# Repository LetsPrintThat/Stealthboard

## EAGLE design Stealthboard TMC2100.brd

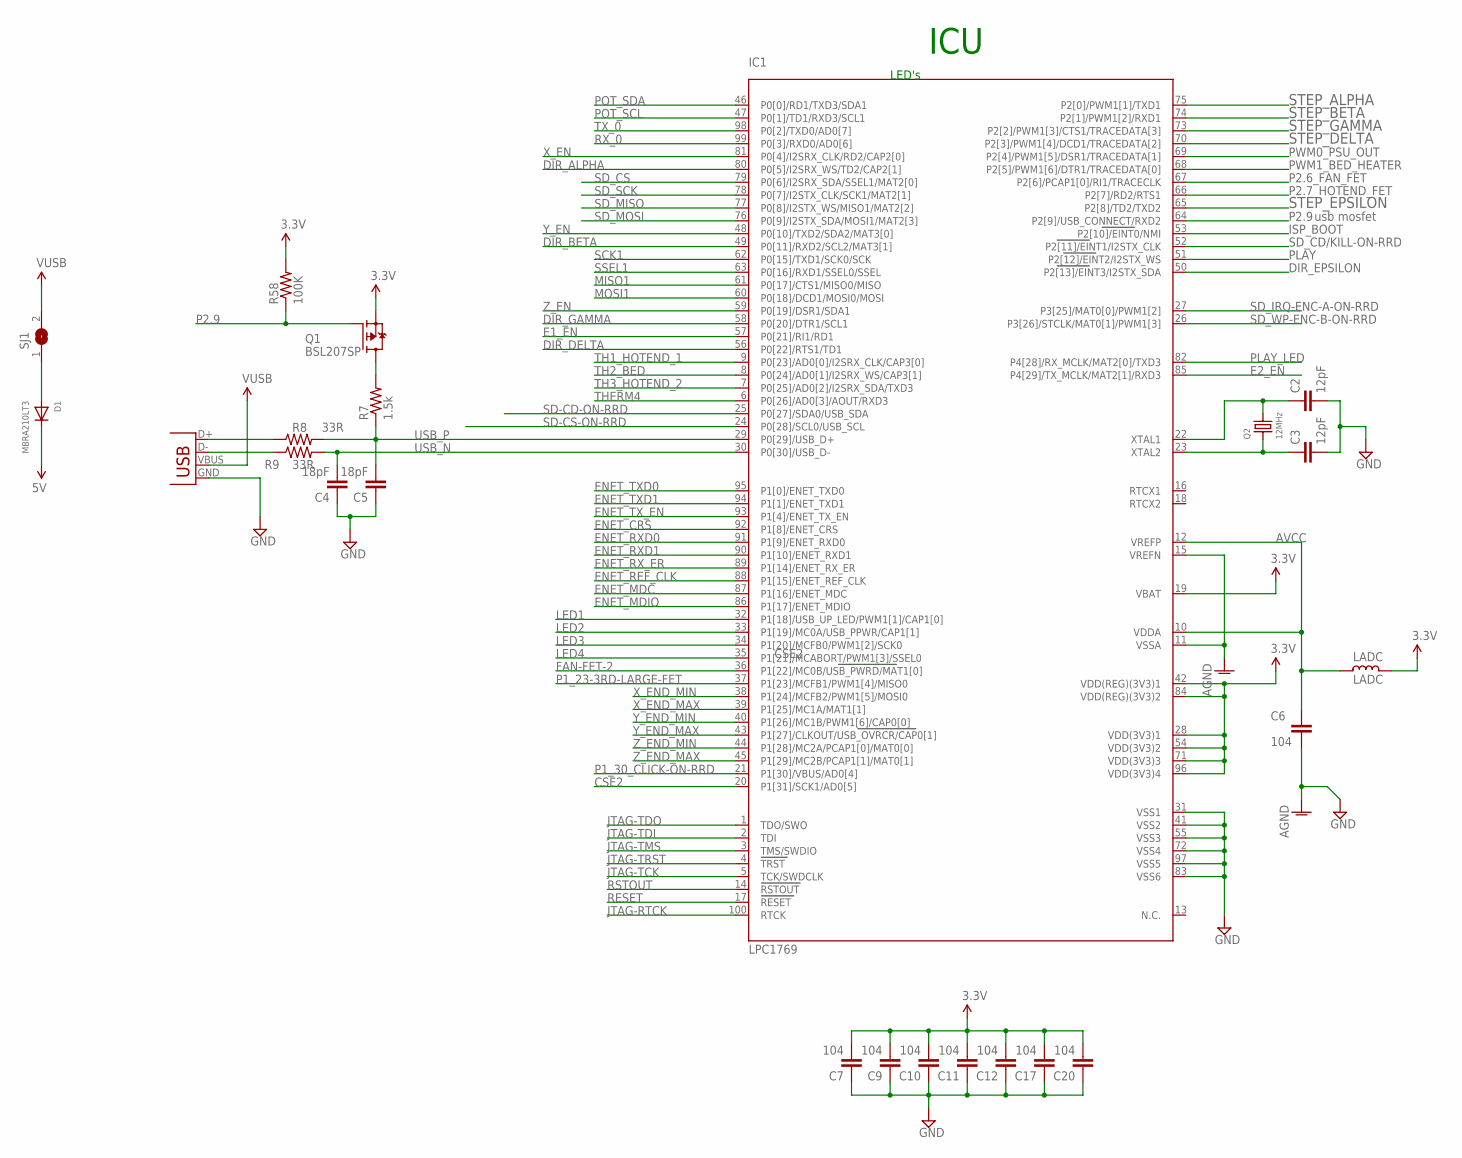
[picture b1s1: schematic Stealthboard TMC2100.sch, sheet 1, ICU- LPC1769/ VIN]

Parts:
C2, C3: 12pF; C0402
C4, C5: 18pF; C0402
C6, C7, C9, C10, C11, C12, C17, C20: 104; C0402
D1: MBRA210LT3; SMADIODE
IC1: LPC1769; LQFP100
LADC: LADC; L0402_LPT
Q1: BSL207SP; SC74_INFINEON
Q2: 12MHz; CRYSTAL_3.2X2.5
R7: 1.5k; R0402
R8, R9: 33R; R0402
R58: 100K; R0402
SJ1: SJ
X14: USBPTH; USB-B-PTH

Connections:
3.3V: C7.2, C9.2, C10.2, C11.2, C12.2, C17.2, C20.2, IC1.19 (VBAT), IC1.28 (VDD(3V3)1), IC1.42 (VDD(REG)(3V3)1), IC1.54 (VDD(3V3)2), IC1.71 (VDD(3V3)3), IC1.84 (VDD(REG)(3V3)2), IC1.96 (VDD(3V3)4), LADC.1, Q1.4 (S), R58.2; also elsewhere on the board
5V: D1.C; also elsewhere on the board
AGND: C6.2, IC1.11 (VSSA), IC1.15 (VREFN); also elsewhere on the board
AVCC: C6.1, IC1.10 (VDDA), IC1.12 (VREFP), LADC.2; also elsewhere on the board
CSE2: IC1.20 (P1[31]/SCK1/AD0[5])
DIR_ALPHA: IC1.80 (P0[5]/I2SRX_WS/TD2/CAP2[1]); also elsewhere on the board
DIR_BETA: IC1.49 (P0[11]/RXD2/SCL2/MAT3[1]); also elsewhere on the board
DIR_DELTA: IC1.56 (P0[22]/RTS1/TD1); also elsewhere on the board
DIR_EPSILON: IC1.50 (P2[13]/EINT3/I2STX_SDA); also elsewhere on the board
DIR_GAMMA: IC1.58 (P0[20]/DTR1/SCL1); also elsewhere on the board
E1_EN: IC1.57 (P0[21]/RI1/RD1); also elsewhere on the board
E2_EN: IC1.85 (P4[29]/TX_MCLK/MAT2[1]/RXD3); also elsewhere on the board
ENET_CRS: IC1.92 (P1[8]/ENET_CRS); also elsewhere on the board
ENET_MDC: IC1.87 (P1[16]/ENET_MDC); also elsewhere on the board
ENET_MDIO: IC1.86 (P1[17]/ENET_MDIO); also elsewhere on the board
ENET_REF_CLK: IC1.88 (P1[15]/ENET_REF_CLK); also elsewhere on the board
ENET_RXD0: IC1.91 (P1[9]/ENET_RXD0); also elsewhere on the board
ENET_RXD1: IC1.90 (P1[10]/ENET_RXD1); also elsewhere on the board
ENET_RX_ER: IC1.89 (P1[14]/ENET_RX_ER)
ENET_TXD0: IC1.95 (P1[0]/ENET_TXD0); also elsewhere on the board
ENET_TXD1: IC1.94 (P1[1]/ENET_TXD1); also elsewhere on the board
ENET_TX_EN: IC1.93 (P1[4]/ENET_TX_EN); also elsewhere on the board
FAN-FET-2: IC1.36 (P1[22]/MC0B/USB_PWRD/MAT1[0]); also elsewhere on the board
GND: C2.2, C3.2, C4.1, C5.1, C7.1, C9.1, C10.1, C11.1, C12.1, C17.1, C20.1, IC1.31 (VSS1), IC1.41 (VSS2), IC1.55 (VSS3), IC1.72 (VSS4), IC1.83 (VSS6), IC1.97 (VSS5), X14.GND; also elsewhere on the board
ISP_BOOT: IC1.53 (P2[10]/EINT0/NMI); also elsewhere on the board
JTAG-RTCK: IC1.100 (RTCK)
JTAG-TCK: IC1.5 (TCK/SWDCLK)
JTAG-TDI: IC1.2 (TDI)
JTAG-TDO: IC1.1 (TDO/SWO)
JTAG-TMS: IC1.3 (TMS/SWDIO)
JTAG-TRST: IC1.4 (TRST)
LED1: IC1.32 (P1[18]/USB_UP_LED/PWM1[1]/CAP1[0]); also elsewhere on the board
LED2: IC1.33 (P1[19]/MC0A/USB_PPWR/CAP1[1]); also elsewhere on the board
LED3: IC1.34 (P1[20]/MCFB0/PWM1[2]/SCK0); also elsewhere on the board
LED4: IC1.35 (P1[21]/MCABORT/PWM1[3]/SSEL0); also elsewhere on the board
MISO1: IC1.61 (P0[17]/CTS1/MISO0/MISO); also elsewhere on the board
MOSI1: IC1.60 (P0[18]/DCD1/MOSI0/MOSI); also elsewhere on the board
unnamed: C2.1, IC1.22 (XTAL1), Q2.2
unnamed: C3.1, IC1.23 (XTAL2), Q2.1
unnamed: D1.A, SJ1.1
unnamed: Q1.1 (D), Q1.2 (D), Q1.5 (D), Q1.6 (D), R7.2
unnamed: R8.1, X14.D+
unnamed: R9.1, X14.D-
P1_23-3RD-LARGE-FET: IC1.37 (P1[23]/MCFB1/PWM1[4]/MISO0); also elsewhere on the board
P1_30_CLICK-ON-RRD: IC1.21 (P1[30]/VBUS/AD0[4]); also elsewhere on the board
P2.6_FAN_FET: IC1.67 (P2[6]/PCAP1[0]/RI1/TRACECLK); also elsewhere on the board
P2.7_HOTEND_FET: IC1.66 (P2[7]/RD2/RTS1); also elsewhere on the board
P2.9: IC1.64 (P2[9]/USB_CONNECT/RXD2), Q1.3 (G), R58.1
PLAY: IC1.51 (P2[12]/EINT2/I2STX_WS); also elsewhere on the board
PLAY_LED: IC1.82 (P4[28]/RX_MCLK/MAT2[0]/TXD3); also elsewhere on the board
POT_SCL: IC1.47 (P0[1]/TD1/RXD3/SCL1); also elsewhere on the board
POT_SDA: IC1.46 (P0[0]/RD1/TXD3/SDA1); also elsewhere on the board
PWM0_PSU_OUT: IC1.69 (P2[4]/PWM1[5]/DSR1/TRACEDATA[1]); also elsewhere on the board
PWM1_BED_HEATER: IC1.68 (P2[5]/PWM1[6]/DTR1/TRACEDATA[0]); also elsewhere on the board
RESET: IC1.17 (RESET); also elsewhere on the board
RSTOUT: IC1.14 (RSTOUT)
RX_0: IC1.99 (P0[3]/RXD0/AD0[6]); also elsewhere on the board
SCK1: IC1.62 (P0[15]/TXD1/SCK0/SCK); also elsewhere on the board
SD-CD-ON-RRD: IC1.25 (P0[27]/SDA0/USB_SDA); also elsewhere on the board
SD-CS-ON-RRD: IC1.24 (P0[28]/SCL0/USB_SCL); also elsewhere on the board
SD_CD/KILL-ON-RRD: IC1.52 (P2[11]/EINT1/I2STX_CLK); also elsewhere on the board
SD_CS: IC1.79 (P0[6]/I2SRX_SDA/SSEL1/MAT2[0]); also elsewhere on the board
SD_IRQ-ENC-A-ON-RRD: IC1.27 (P3[25]/MAT0[0]/PWM1[2]); also elsewhere on the board
SD_MISO: IC1.77 (P0[8]/I2STX_WS/MISO1/MAT2[2]); also elsewhere on the board
SD_MOSI: IC1.76 (P0[9]/I2STX_SDA/MOSI1/MAT2[3]); also elsewhere on the board
SD_SCK: IC1.78 (P0[7]/I2STX_CLK/SCK1/MAT2[1]); also elsewhere on the board
SD_WP-ENC-B-ON-RRD: IC1.26 (P3[26]/STCLK/MAT0[1]/PWM1[3]); also elsewhere on the board
SSEL1: IC1.63 (P0[16]/RXD1/SSEL0/SSEL); also elsewhere on the board
STEP_ALPHA: IC1.75 (P2[0]/PWM1[1]/TXD1); also elsewhere on the board
STEP_BETA: IC1.74 (P2[1]/PWM1[2]/RXD1); also elsewhere on the board
STEP_DELTA: IC1.70 (P2[3]/PWM1[4]/DCD1/TRACEDATA[2]); also elsewhere on the board
STEP_EPSILON: IC1.65 (P2[8]/TD2/TXD2); also elsewhere on the board
STEP_GAMMA: IC1.73 (P2[2]/PWM1[3]/CTS1/TRACEDATA[3]); also elsewhere on the board
TH1_HOTEND_1: IC1.9 (P0[23]/AD0[0]/I2SRX_CLK/CAP3[0]); also elsewhere on the board
TH2_BED: IC1.8 (P0[24]/AD0[1]/I2SRX_WS/CAP3[1]); also elsewhere on the board
TH3_HOTEND_2: IC1.7 (P0[25]/AD0[2]/I2SRX_SDA/TXD3); also elsewhere on the board
THERM4: IC1.6 (P0[26]/AD0[3]/AOUT/RXD3)
TX_0: IC1.98 (P0[2]/TXD0/AD0[7]); also elsewhere on the board
USB_N: C4.2, IC1.30 (P0[30]/USB_D-), R9.2
USB_P: C5.2, IC1.29 (P0[29]/USB_D+), R7.1, R8.2
VUSB: SJ1.2, X14.VBUS
X_EN: IC1.81 (P0[4]/I2SRX_CLK/RD2/CAP2[0]); also elsewhere on the board
X_END_MAX: IC1.39 (P1[25]/MC1A/MAT1[1])
X_END_MIN: IC1.38 (P1[24]/MCFB2/PWM1[5]/MOSI0); also elsewhere on the board
Y_EN: IC1.48 (P0[10]/TXD2/SDA2/MAT3[0]); also elsewhere on the board
Y_END_MAX: IC1.43 (P1[27]/CLKOUT/USB_OVRCR/CAP0[1])
Y_END_MIN: IC1.40 (P1[26]/MC1B/PWM1[6]/CAP0[0]); also elsewhere on the board
Z_EN: IC1.59 (P0[19]/DSR1/SDA1); also elsewhere on the board
Z_END_MAX: IC1.45 (P1[29]/MC2B/PCAP1[1]/MAT0[1]); also elsewhere on the board
Z_END_MIN: IC1.44 (P1[28]/MC2A/PCAP1[0]/MAT0[0]); also elsewhere on the board

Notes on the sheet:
usb mosfet
LED's
ICU

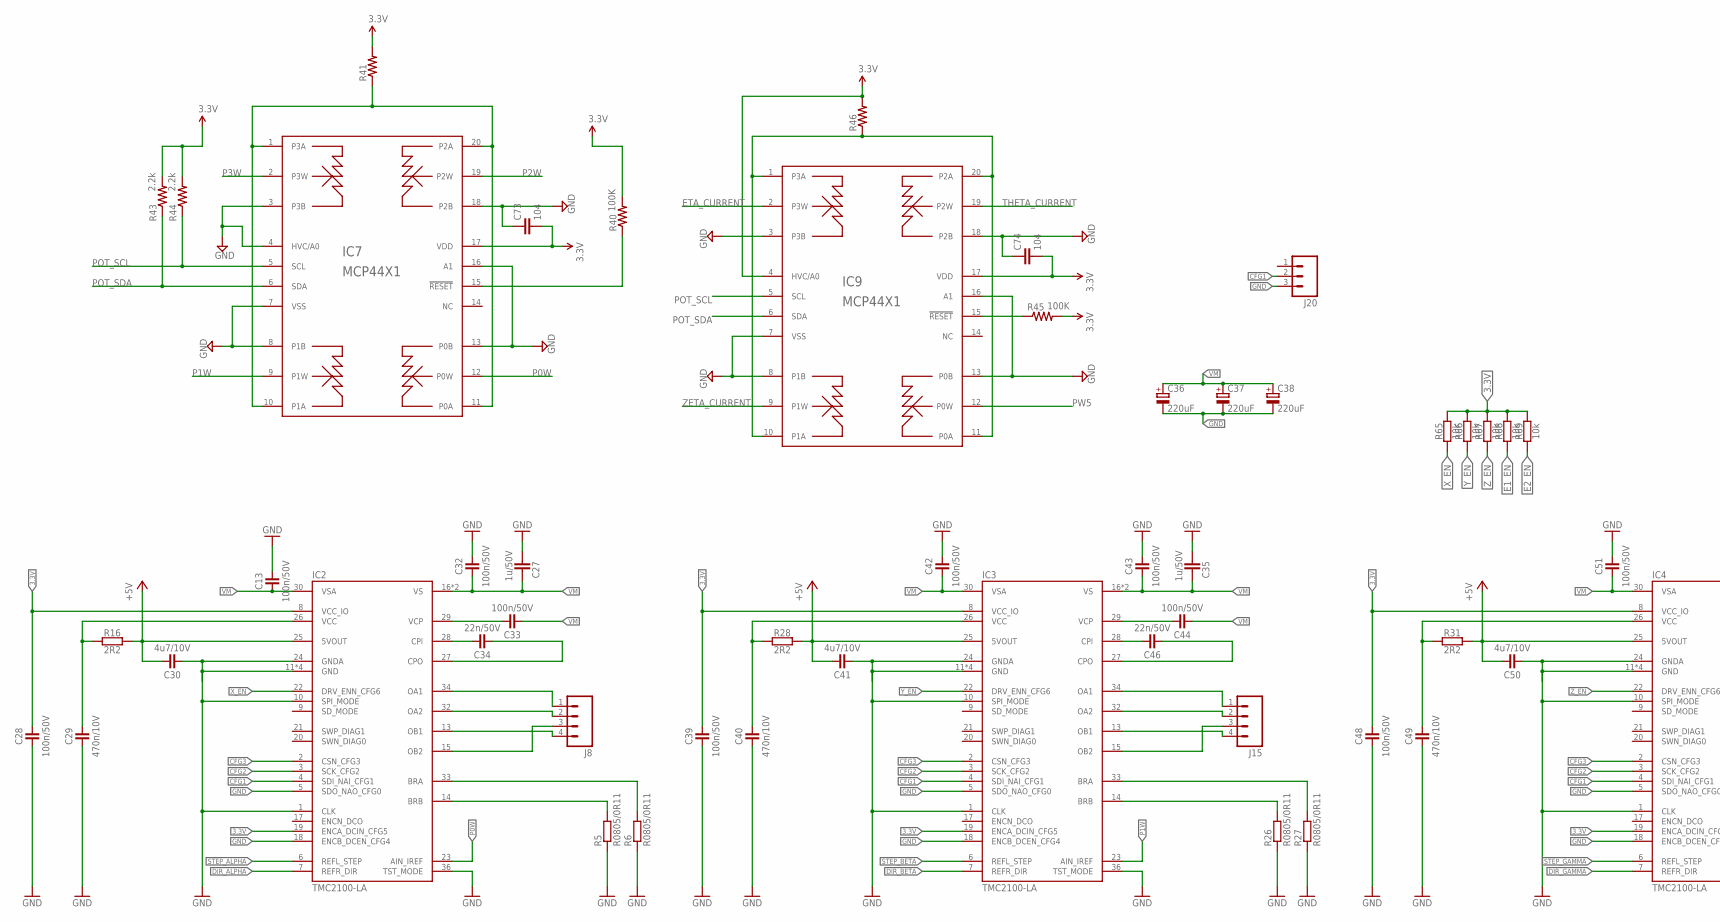
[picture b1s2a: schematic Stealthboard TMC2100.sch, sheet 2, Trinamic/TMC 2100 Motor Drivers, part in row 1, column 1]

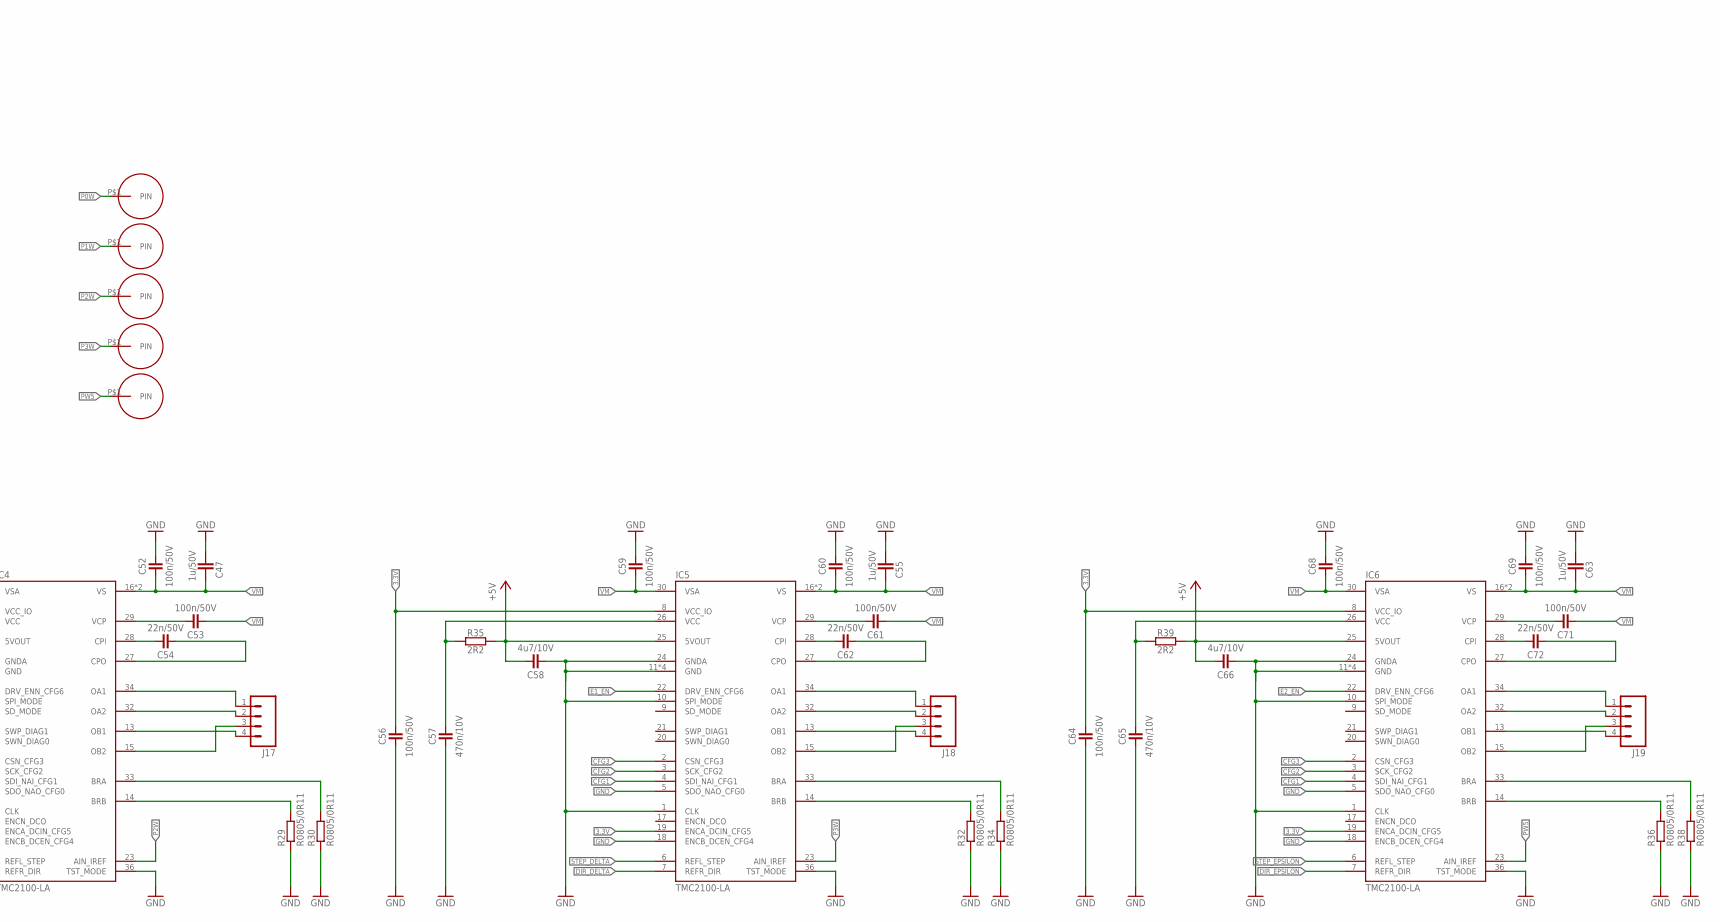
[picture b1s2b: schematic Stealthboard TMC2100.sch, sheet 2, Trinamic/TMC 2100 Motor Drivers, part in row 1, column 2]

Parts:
C13, C28, C32, C33, C39, C42, C43, C44, C48, C51, C52, C53, C56, C59, C60, C61, C64, C68, C69, C71: 100n/50V; C0402
C27, C35, C47, C55, C63: 1u/50V; C0603
C29, C40, C49, C57, C65: 470n/10V; C0402
C30, C41, C50, C58, C66: 4u7/10V; C0402
C34, C46, C54, C62, C72: 22n/50V; C0402
C36, C37, C38: 220uF; 153CLV-0807
C73, C74: 104; C0402
IC2, IC3, IC4, IC5, IC6: TMC2100-LA; QFN36-PAD
IC7, IC9: MCP44X1; TSSOP20
J8, J15, J17, J18, J19: M04POLAR_LOCK; MOLEX-1X4_LOCK
J20: M03PTH; 1X03
R5, R6, R26, R27, R29, R30, R32, R34, R36, R38: R0805/0R11; M0805
R16, R28, R31, R35, R39: 2R2; C0402
R40, R45: 100K; R0402
R41, R46: R-US_R0402; R0402
R43, R44: 2.2k; R0402
R65, R66, R67, R68, R69: 10k; C0402
U$8, U$9, U$10, U$11, U$12: SMALL_PAD

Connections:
3.3V: C28.2, C39.2, C48.2, C56.2, C64.2, C73.2, C74.2, IC2.8 (VCC_IO), IC2.19 (ENCA_DCIN_CFG5), IC3.8 (VCC_IO), IC3.19 (ENCA_DCIN_CFG5), IC4.8 (VCC_IO), IC4.19 (ENCA_DCIN_CFG5), IC5.8 (VCC_IO), IC5.19 (ENCA_DCIN_CFG5), IC6.8 (VCC_IO), IC6.19 (ENCA_DCIN_CFG5), IC7.17 (VDD), IC9.4 (HVC/A0), IC9.17 (VDD), R40.2, R41.2, R43.2, R44.2, R45.2, R46.2, R65.2, R66.2, R67.2, R68.2, R69.2; also elsewhere on the board
+5V: C30.2, C41.2, C50.2, C58.2, C66.2, IC2.25 (5VOUT), IC3.25 (5VOUT), IC4.25 (5VOUT), IC5.25 (5VOUT), IC6.25 (5VOUT), R16.2, R28.2, R31.2, R35.2, R39.2
BRA: IC2.33 (BRA), R6.2
BRA1: IC3.33 (BRA), R27.2
BRA2: IC4.33 (BRA), R30.2
BRA3: IC5.33 (BRA), R34.2
BRA4: IC6.33 (BRA), R38.2
BRB: IC2.14 (BRB), R5.2
BRB1: IC3.14 (BRB), R26.2
BRB2: IC4.14 (BRB), R29.2
BRB3: IC5.14 (BRB), R32.2
BRB4: IC6.14 (BRB), R36.2
CFG1: IC2.4 (SDI_NAI_CFG1), IC3.4 (SDI_NAI_CFG1), IC4.4 (SDI_NAI_CFG1), IC5.4 (SDI_NAI_CFG1), IC6.4 (SDI_NAI_CFG1), J20.2
CFG2: IC2.3 (SCK_CFG2), IC3.3 (SCK_CFG2), IC4.3 (SCK_CFG2), IC5.3 (SCK_CFG2), IC6.3 (SCK_CFG2)
CFG3: IC2.2 (CSN_CFG3), IC3.2 (CSN_CFG3), IC4.2 (CSN_CFG3), IC5.2 (CSN_CFG3), IC6.2 (CSN_CFG3)
CPI: C34.2, IC2.28 (CPI)
CPI1: C46.2, IC3.28 (CPI)
CPI2: C54.2, IC4.28 (CPI)
CPI3: C62.2, IC5.28 (CPI)
CPI4: C72.2, IC6.28 (CPI)
CPO: C34.1, IC2.27 (CPO)
CPO1: C46.1, IC3.27 (CPO)
CPO2: C54.1, IC4.27 (CPO)
CPO3: C62.1, IC5.27 (CPO)
CPO4: C72.1, IC6.27 (CPO)
DIR_ALPHA: IC2.7 (REFR_DIR); also elsewhere on the board
DIR_BETA: IC3.7 (REFR_DIR); also elsewhere on the board
DIR_DELTA: IC5.7 (REFR_DIR); also elsewhere on the board
DIR_EPSILON: IC6.7 (REFR_DIR); also elsewhere on the board
DIR_GAMMA: IC4.7 (REFR_DIR); also elsewhere on the board
E1_EN: IC5.22 (DRV_ENN_CFG6), R68.1; also elsewhere on the board
E2_EN: IC6.22 (DRV_ENN_CFG6), R69.1; also elsewhere on the board
ETA_CURRENT: IC9.2 (P3W)
GND: C13.2, C27.2, C28.1, C29.1, C30.1, C32.2, C35.2, C36.-, C37.-, C38.-, C39.1, C40.1, C41.1, C42.2, C43.2, C47.2, C48.1, C49.1, C50.1, C51.2, C52.2, C55.2, C56.1, C57.1, C58.1, C59.2, C60.2, C63.2, C64.1, C65.1, C66.1, C68.2, C69.2, C73.1, C74.1, IC2.1 (CLK), IC2.5 (SDO_NAO_CFG0), IC2.10 (SPI_MODE), IC2.11 (GND), IC2.12 (GND), IC2.18 (ENCB_DCEN_CFG4), IC2.24 (GNDA), IC2.35 (GND), IC2.36 (TST_MODE), IC2.TP (GND), IC3.1 (CLK), IC3.5 (SDO_NAO_CFG0), IC3.10 (SPI_MODE), IC3.11 (GND), IC3.12 (GND), IC3.18 (ENCB_DCEN_CFG4), IC3.24 (GNDA), IC3.35 (GND), IC3.36 (TST_MODE), IC3.TP (GND), IC4.1 (CLK), IC4.5 (SDO_NAO_CFG0), IC4.10 (SPI_MODE), IC4.11 (GND), IC4.12 (GND), IC4.18 (ENCB_DCEN_CFG4), IC4.24 (GNDA), IC4.35 (GND), IC4.36 (TST_MODE), IC4.TP (GND), IC5.1 (CLK), IC5.5 (SDO_NAO_CFG0), IC5.10 (SPI_MODE), IC5.11 (GND), IC5.12 (GND), IC5.18 (ENCB_DCEN_CFG4), IC5.24 (GNDA), IC5.35 (GND), IC5.36 (TST_MODE), IC5.TP (GND), IC6.1 (CLK), IC6.5 (SDO_NAO_CFG0), IC6.10 (SPI_MODE), IC6.11 (GND), IC6.12 (GND), IC6.18 (ENCB_DCEN_CFG4), IC6.24 (GNDA), IC6.35 (GND), IC6.36 (TST_MODE), IC6.TP (GND), IC7.3 (P3B), IC7.4 (HVC/A0), IC7.7 (VSS), IC7.8 (P1B), IC7.13 (P0B), IC7.16 (A1), IC7.18 (P2B), IC9.3 (P3B), IC9.7 (VSS), IC9.8 (P1B), IC9.13 (P0B), IC9.16 (A1), IC9.18 (P2B), J20.3, R5.1, R6.1, R26.1, R27.1, R29.1, R30.1, R32.1, R34.1, R36.1, R38.1; also elsewhere on the board
unnamed: IC7.15 (!RESET), R40.1
unnamed: IC7.1 (P3A), IC7.10 (P1A), IC7.11 (P0A), IC7.20 (P2A), R41.1
unnamed: IC9.15 (!RESET), R45.1
unnamed: C29.2, IC2.26 (VCC), R16.1
unnamed: IC9.1 (P3A), IC9.10 (P1A), IC9.11 (P0A), IC9.20 (P2A), R46.1
OA1: IC2.34 (OA1), IC3.34 (OA1), IC4.34 (OA1), IC5.34 (OA1), IC6.34 (OA1), J8.1, J15.1, J17.1, J18.1, J19.1
OA2: IC2.32 (OA2), IC3.32 (OA2), IC4.32 (OA2), IC5.32 (OA2), IC6.32 (OA2), J8.2, J15.2, J17.2, J18.2, J19.2
OB1: IC2.13 (OB1), IC3.13 (OB1), IC4.13 (OB1), IC5.13 (OB1), IC6.13 (OB1), J8.4, J15.4, J17.4, J18.4, J19.4
OB2: IC2.15 (OB2), IC3.15 (OB2), IC4.15 (OB2), IC5.15 (OB2), IC6.15 (OB2), J8.3, J15.3, J17.3, J18.3, J19.3
P0W: IC2.23 (AIN_IREF), IC7.12 (P0W), U$8.P$1
P1W: IC3.23 (AIN_IREF), IC7.9 (P1W), U$9.P$1
P2W: IC4.23 (AIN_IREF), IC7.19 (P2W), U$10.P$1
P3W: IC5.23 (AIN_IREF), IC7.2 (P3W), U$11.P$1
POT_SCL: IC7.5 (SCL), IC9.5 (SCL), R44.1; also elsewhere on the board
POT_SDA: IC7.6 (SDA), IC9.6 (SDA), R43.1; also elsewhere on the board
PW5: IC6.23 (AIN_IREF), IC9.12 (P0W), U$12.P$1
STEP_ALPHA: IC2.6 (REFL_STEP); also elsewhere on the board
STEP_BETA: IC3.6 (REFL_STEP); also elsewhere on the board
STEP_DELTA: IC5.6 (REFL_STEP); also elsewhere on the board
STEP_EPSILON: IC6.6 (REFL_STEP); also elsewhere on the board
STEP_GAMMA: IC4.6 (REFL_STEP); also elsewhere on the board
THETA_CURRENT: IC9.19 (P2W)
VCC1: C40.2, IC3.26 (VCC), R28.1
VCC2: C49.2, IC4.26 (VCC), R31.1
VCC3: C57.2, IC5.26 (VCC), R35.1
VCC4: C65.2, IC6.26 (VCC), R39.1
VCP: C33.2, IC2.29 (VCP)
VCP1: C44.2, IC3.29 (VCP)
VCP2: C53.2, IC4.29 (VCP)
VCP3: C61.2, IC5.29 (VCP)
VCP4: C71.2, IC6.29 (VCP)
VM: C13.1, C27.1, C32.1, C33.1, C35.1, C36.+, C37.+, C38.+, C42.1, C43.1, C44.1, C47.1, C51.1, C52.1, C53.1, C55.1, C59.1, C60.1, C61.1, C63.1, C68.1, C69.1, C71.1, IC2.16 (VS), IC2.30 (VSA), IC2.31 (VS), IC3.16 (VS), IC3.30 (VSA), IC3.31 (VS), IC4.16 (VS), IC4.30 (VSA), IC4.31 (VS), IC5.16 (VS), IC5.30 (VSA), IC5.31 (VS), IC6.16 (VS), IC6.30 (VSA), IC6.31 (VS); also elsewhere on the board
X_EN: IC2.22 (DRV_ENN_CFG6), R65.1; also elsewhere on the board
Y_EN: IC3.22 (DRV_ENN_CFG6), R66.1; also elsewhere on the board
ZETA_CURRENT: IC9.9 (P1W)
Z_EN: IC4.22 (DRV_ENN_CFG6), R67.1; also elsewhere on the board

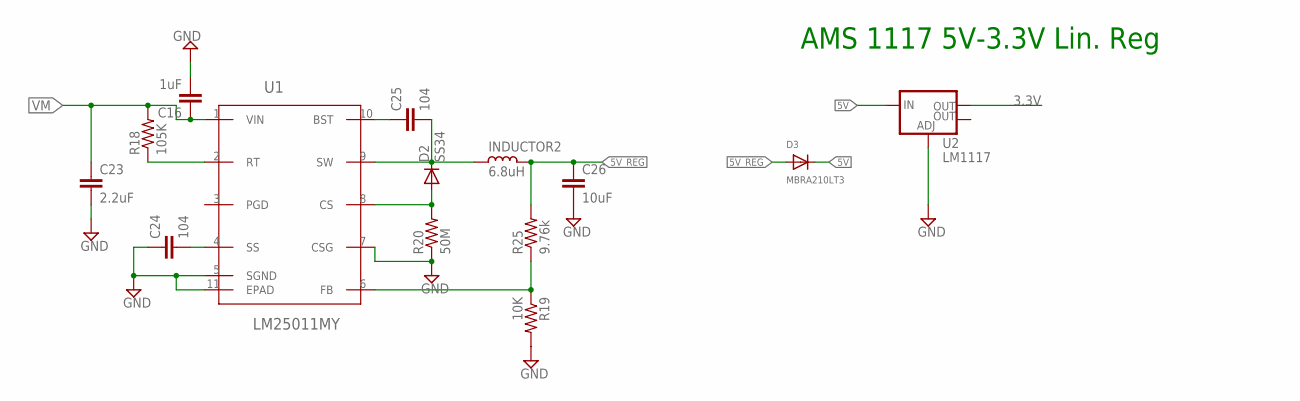
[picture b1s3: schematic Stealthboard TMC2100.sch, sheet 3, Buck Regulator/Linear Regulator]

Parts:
C16: 1uF; C0805
C23: 2.2uF; C1206
C24, C25: 104; C0805
C26: 10uF; C0603
D2: SS34; DO-214AC
D3: MBRA210LT3; SMADIODE
INDUCTOR2: 6.8uH; CD75
R18: 105K; R0402
R19: 10K; R0402
R20: 50M; R0805
R25: 9.76k; R0805
U1: LM25011MY; SOP50P490X110-11N
U2: LM1117; SOT223

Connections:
3.3V: U2.2 (OUT); also elsewhere on the board
5V: D3.C, U2.3 (IN); also elsewhere on the board
5V_REG: C26.1, D3.A, INDUCTOR2.1, R25.2
GND: C16.2, C23.2, C24.1, C26.2, R19.2, R20.1, U1.5 (SGND), U1.7 (CSG), U1.11 (EPAD), U2.1 (ADJ); also elsewhere on the board
unnamed: R18.1, U1.2 (RT)
unnamed: R19.1, R25.1, U1.6 (FB)
unnamed: C24.2, U1.4 (SS)
unnamed: C25.1, U1.10 (BST)
unnamed: C25.2, D2.1 (C), INDUCTOR2.2, U1.9 (SW)
unnamed: D2.2 (A), R20.2, U1.8 (CS)
VM: C16.1, C23.1, R18.2, U1.1 (VIN); also elsewhere on the board

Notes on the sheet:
AMS 1117 5V-3.3V Lin. Reg

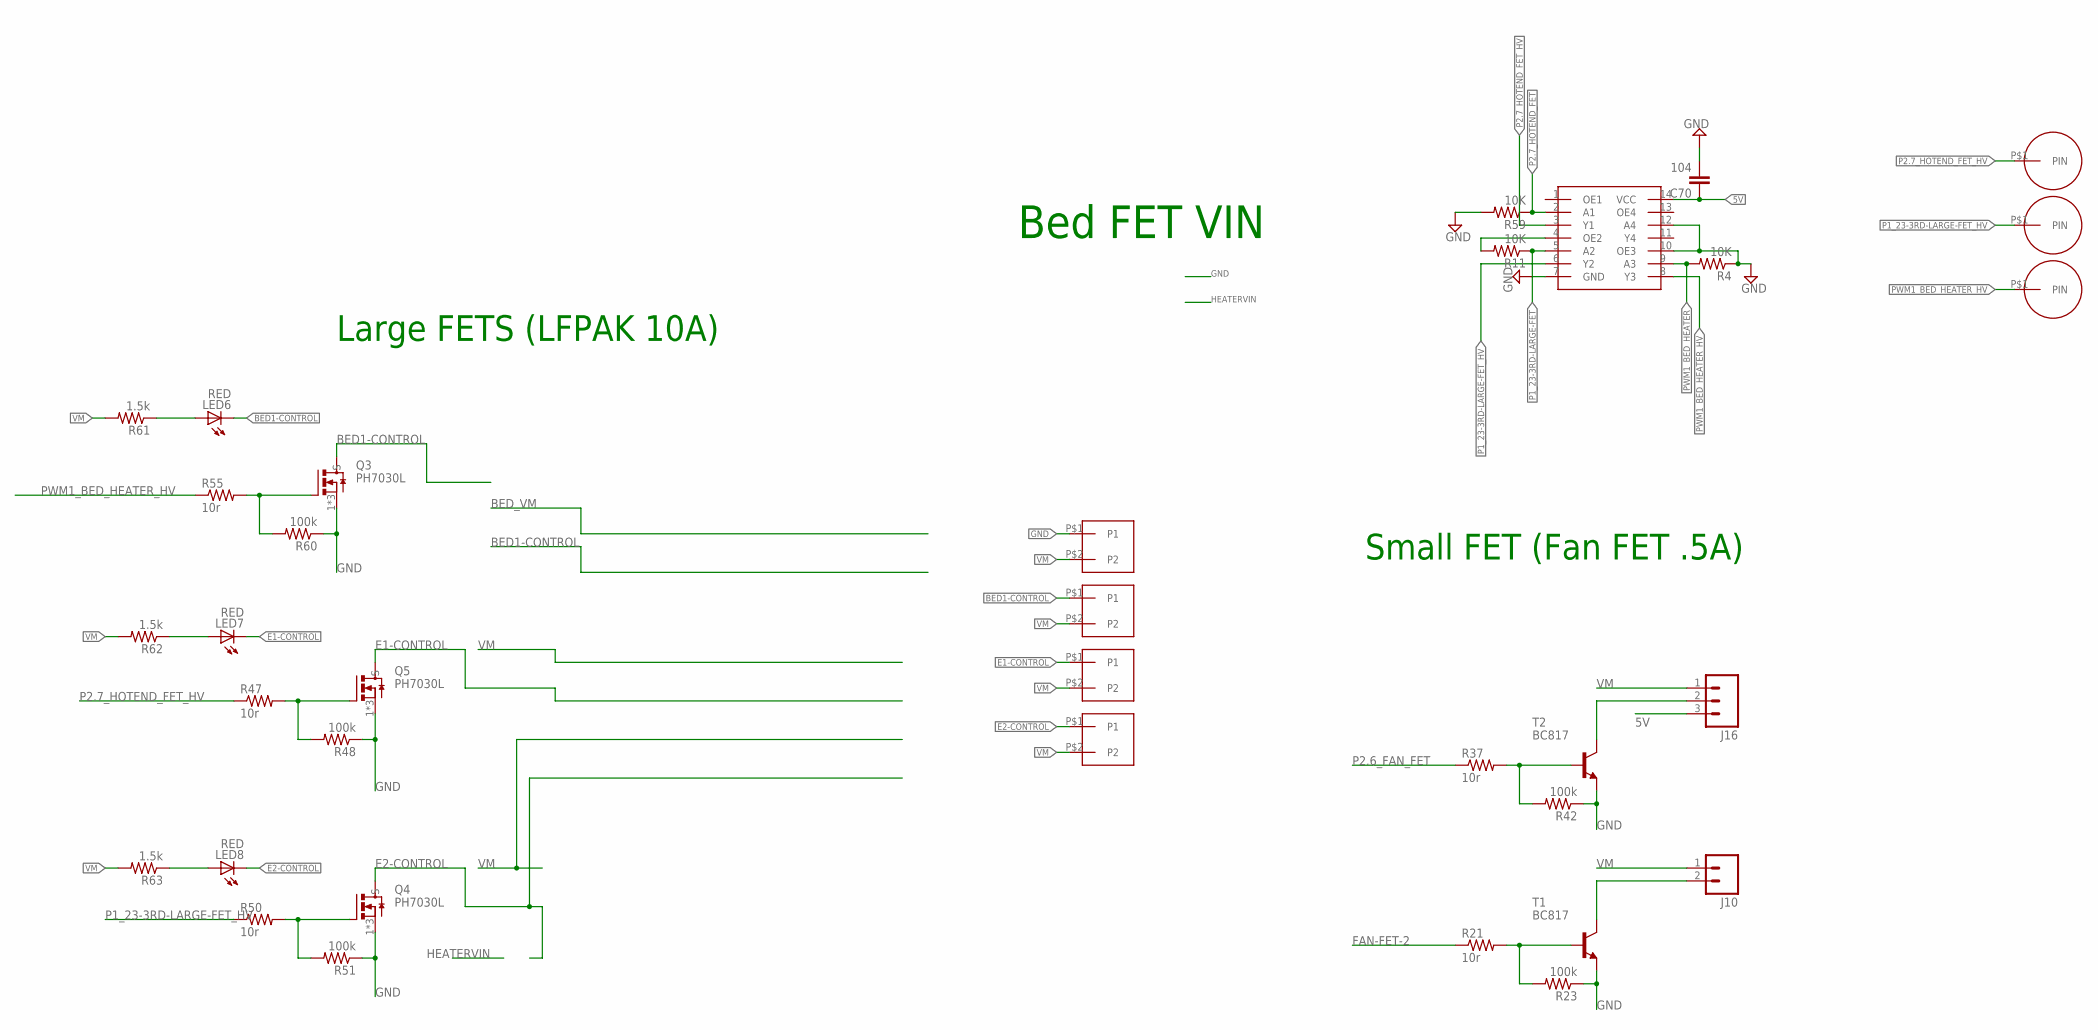
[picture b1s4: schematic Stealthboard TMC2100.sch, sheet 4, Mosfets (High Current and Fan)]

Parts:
C70: 104; C0402
J10: M02POLAR_LOCK; MOLEX-1X2_LOCK
J16: M03POLAR_LOCK; MOLEX-1X3_LOCK
LED6, LED7, LED8: RED; CHIP-LED0603
Q3, Q4, Q5: PH7030L; SOT669
R4, R11, R59: 10K; R0402
R21, R37, R47, R50, R55: 10r; R0402
R23, R42, R48, R51, R60: 100k; R0402
R61, R62, R63: 1.5k; R0402
T1, T2: BC817; SOT23-BEC
U$1, U$4, U$5, U$6: KF635-6.35MM-2PKF635-2P; KF635-6.35MM
U$2: MC74VHCT125ADTRG; TSSOP-14
U$7, U$13, U$14: SMALL_PAD

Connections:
5V: C70.1, J16.3, U$2.14 (VCC); also elsewhere on the board
BED1-CONTROL: LED6.C, Q3.MB (D), U$4.P$1 (P1)
E1-CONTROL: LED7.C, Q5.MB (D), U$1.P$1 (P1)
E2-CONTROL: LED8.C, Q4.MB (D), U$6.P$1 (P1)
FAN-FET-2: R21.1; also elsewhere on the board
GND: C70.2, Q3.1 (S), Q3.2 (S), Q3.3 (S), Q4.1 (S), Q4.2 (S), Q4.3 (S), Q5.1 (S), Q5.2 (S), Q5.3 (S), R4.1, R23.1, R42.1, R48.1, R51.1, R59.2, R60.1, T1.E, T2.E, U$2.7 (GND), U$2.10 (OE3), U$2.12 (A4), U$5.P$1 (P1); also elsewhere on the board
unnamed: J10.2, T1.C
unnamed: Q3.4 (G), R55.2, R60.2
unnamed: R37.2, R42.2, T2.B
unnamed: R21.2, R23.2, T1.B
unnamed: Q5.4 (G), R47.2, R48.2
unnamed: J16.2, T2.C
unnamed: Q4.4 (G), R50.2, R51.2
unnamed: LED6.A, R61.1
unnamed: LED7.A, R62.1
unnamed: LED8.A, R63.1
unnamed: R11.2, U$2.4 (OE2)
P1_23-3RD-LARGE-FET: R11.1, U$2.5 (A2); also elsewhere on the board
P1_23-3RD-LARGE-FET_HV: R50.1, U$2.6 (Y2), U$13.P$1
P2.6_FAN_FET: R37.1; also elsewhere on the board
P2.7_HOTEND_FET: R59.1, U$2.2 (A1); also elsewhere on the board
P2.7_HOTEND_FET_HV: R47.1, U$2.3 (Y1), U$7.P$1
PWM1_BED_HEATER: R4.2, U$2.9 (A3); also elsewhere on the board
PWM1_BED_HEATER_HV: R55.1, U$2.8 (Y3), U$14.P$1
VM: J10.1, J16.1, R61.2, R62.2, R63.2, U$1.P$2 (P2), U$4.P$2 (P2), U$5.P$2 (P2), U$6.P$2 (P2); also elsewhere on the board

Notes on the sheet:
Small FET (Fan FET .5A)
Bed FET VIN
Large FETS (LFPAK 10A)

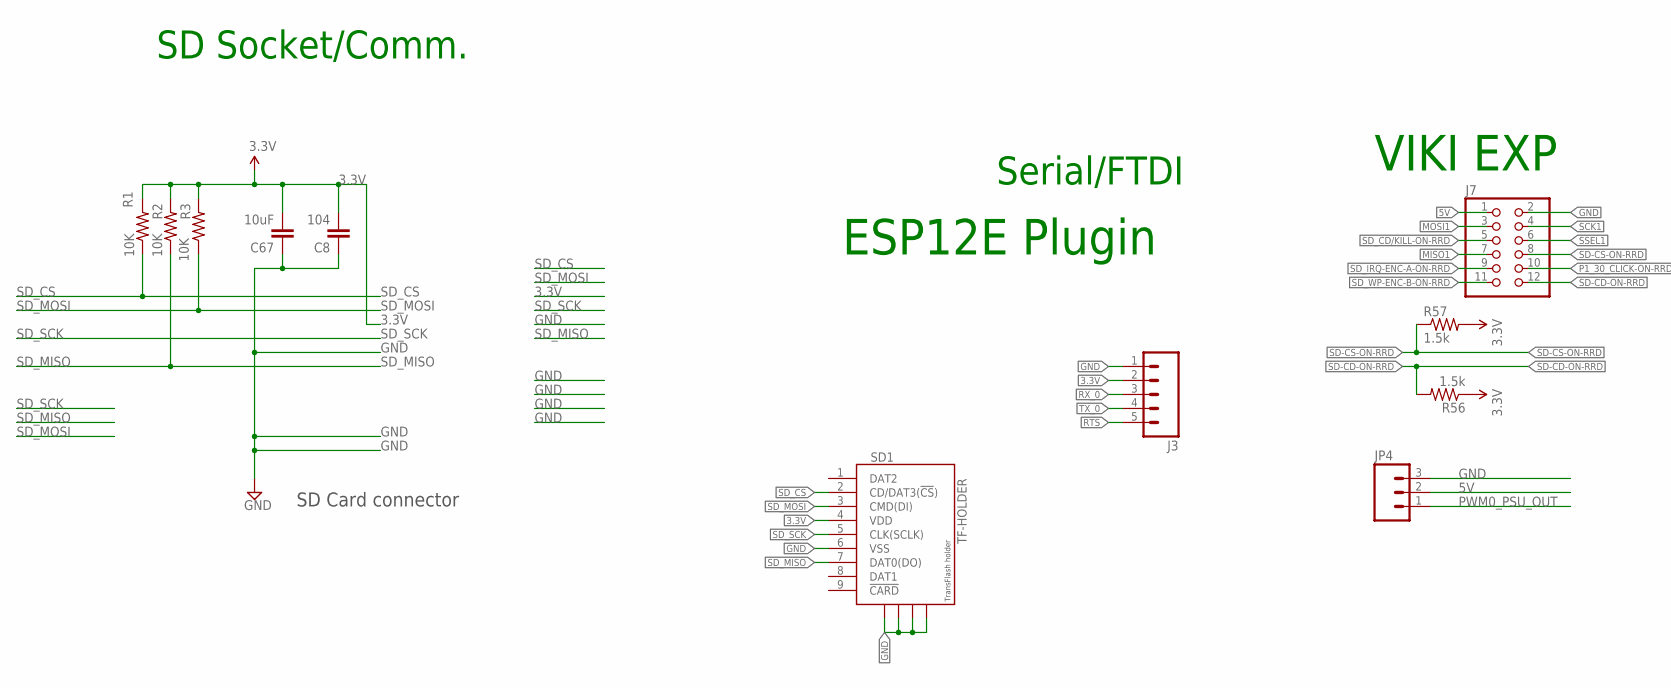
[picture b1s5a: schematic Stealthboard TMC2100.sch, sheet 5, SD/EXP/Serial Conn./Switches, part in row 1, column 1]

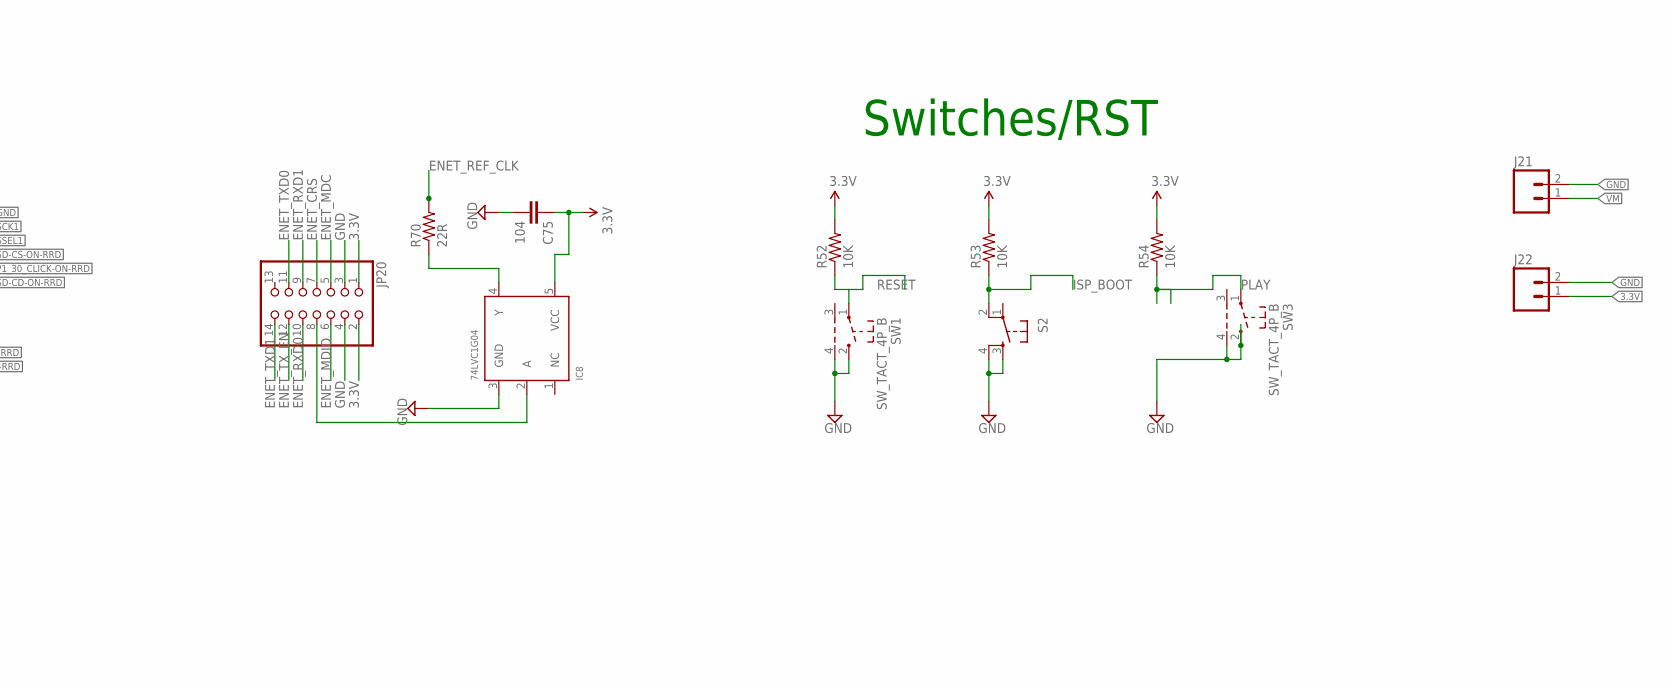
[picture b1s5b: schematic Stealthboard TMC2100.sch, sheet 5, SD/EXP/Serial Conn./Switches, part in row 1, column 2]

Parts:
C8, C75: 104; C0402
C67: 10uF; C0402
IC8: 74LVC1G04; SOT23-5
J3: M05PTH; 1X05
J7: PINHD-2X6; 2X06
J21, J22: M02PTH; 1X02
JP4: M03POLAR_LOCK; MOLEX-1X3_LOCK
JP20: PINHD-2X7; 2X07
R1, R2, R3, R52, R53, R54: 10K; R0402
R56, R57: 1.5k; R0402
R70: 22R; R0402
S2: TAC_SWITCHSMD; TACTILE_SWITCH_SMD
SD1: TF-HOLDER; TF-PULL
SW1, SW3: SW_TACT_4P_B; SW_TACT_STANDARD_RIGHT_ANGLE

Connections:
3.3V: C8.2, C67.2, C75.1, IC8.5 (VCC), J3.2, J22.1, JP20.1, JP20.2, R1.2, R2.2, R3.2, R52.2, R53.2, R54.2, R56.1, R57.2, SD1.4 (VDD); also elsewhere on the board
5V: J7.1, JP4.2; also elsewhere on the board
ENET_CRS: JP20.7; also elsewhere on the board
ENET_MDC: JP20.5; also elsewhere on the board
ENET_MDIO: JP20.6; also elsewhere on the board
ENET_REF_CLK: R70.2; also elsewhere on the board
ENET_RXD0: JP20.10; also elsewhere on the board
ENET_RXD1: JP20.9; also elsewhere on the board
ENET_TXD0: JP20.11; also elsewhere on the board
ENET_TXD1: JP20.14; also elsewhere on the board
ENET_TX_EN: JP20.12; also elsewhere on the board
GND: C8.1, C67.1, C75.2, IC8.3 (GND), J3.1, J7.2, J21.2, J22.2, JP4.3, JP20.3, JP20.4, S2.3, S2.4, SD1.6 (VSS), SD1.S1, SD1.S2, SD1.S3, SD1.S4, SW1.2, SW1.4, SW3.2, SW3.4; also elsewhere on the board
ISP_BOOT: R53.1, S2.2; also elsewhere on the board
MISO1: J7.7; also elsewhere on the board
MOSI1: J7.3; also elsewhere on the board
unnamed: IC8.2 (A), JP20.8
unnamed: IC8.4 (Y), R70.1
P1_30_CLICK-ON-RRD: J7.10; also elsewhere on the board
PLAY: R54.1, SW3.1; also elsewhere on the board
PWM0_PSU_OUT: JP4.1; also elsewhere on the board
RESET: R52.1, SW1.1; also elsewhere on the board
RTS: J3.5
RX_0: J3.3; also elsewhere on the board
SCK1: J7.4; also elsewhere on the board
SD-CD-ON-RRD: J7.12, R56.2; also elsewhere on the board
SD-CS-ON-RRD: J7.8, R57.1; also elsewhere on the board
SD_CD/KILL-ON-RRD: J7.5; also elsewhere on the board
SD_CS: R1.1, SD1.2 (CD/DAT3(!CS!)); also elsewhere on the board
SD_IRQ-ENC-A-ON-RRD: J7.9; also elsewhere on the board
SD_MISO: R2.1, SD1.7 (DAT0(DO)); also elsewhere on the board
SD_MOSI: R3.1, SD1.3 (CMD(DI)); also elsewhere on the board
SD_SCK: SD1.5 (CLK(SCLK)); also elsewhere on the board
SD_WP-ENC-B-ON-RRD: J7.11; also elsewhere on the board
SSEL1: J7.6; also elsewhere on the board
TX_0: J3.4; also elsewhere on the board
VM: J21.1; also elsewhere on the board

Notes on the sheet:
SD Card connector
SD Socket/Comm.
Serial/FTDI
VIKI EXP
Switches/RST
ESP12E Plugin

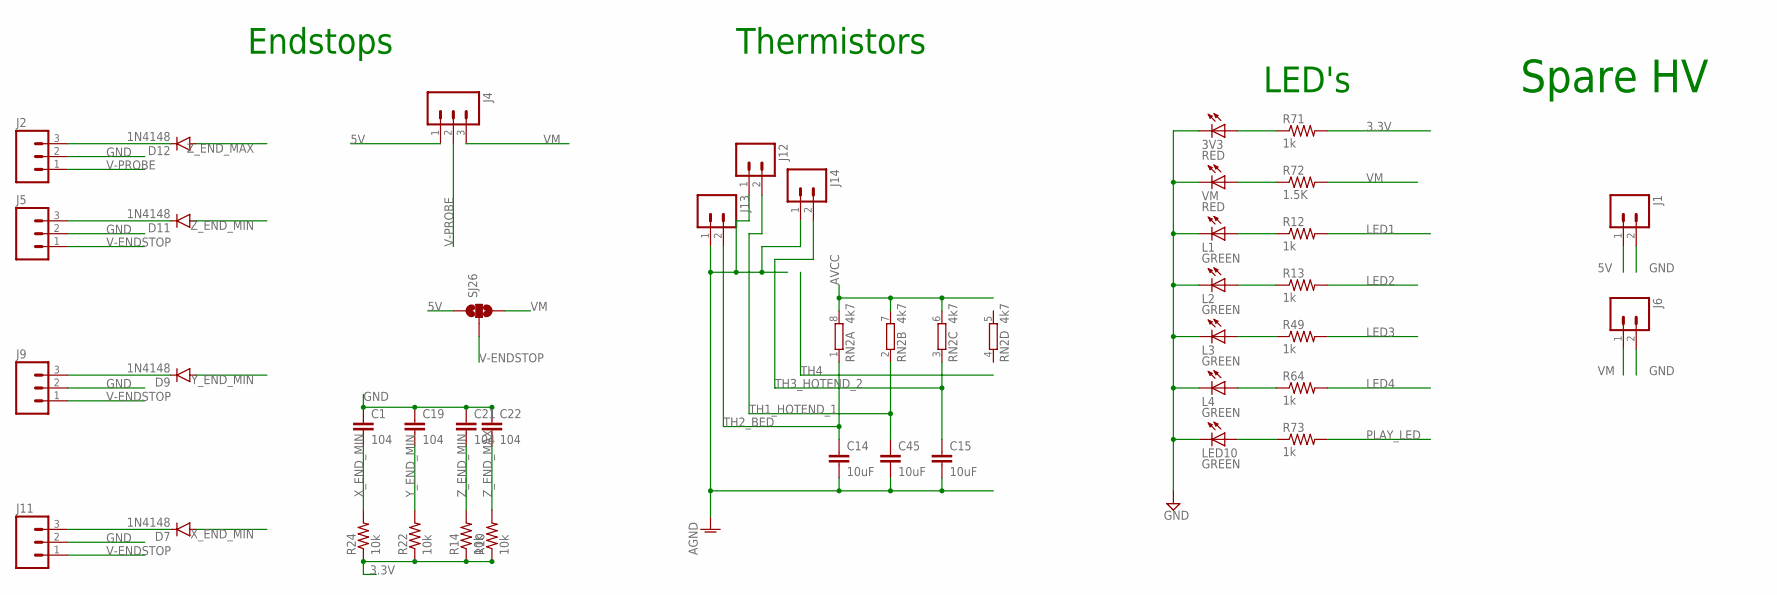
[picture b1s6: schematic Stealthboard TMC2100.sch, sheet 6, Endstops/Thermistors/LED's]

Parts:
3V3: RED; SML0603
C1, C19, C21, C22: 104; C0402
C14, C15, C45: 10uF; C0402
D7, D9, D11, D12: 1N4148; SOD-323
J1, J6, J12, J13, J14: M02POLAR_LOCK; MOLEX-1X2_LOCK
J2, J5, J9, J11: M03POLAR_LOCK; MOLEX-1X3_LOCK
J4: M03PTH; 1X03
L1, L2, L3, L4: GREEN; SML0603
LED10: GREEN; SML0603
R10, R14, R22, R24: 10k; R0402
R12, R13, R49, R64, R71, R73: 1k; R0402
R72: 1.5K; R0402
RN2: 4k7; 0603-ARV
SJ26: SOLDERJUMPER_2WAYS; SJ_3
VM: RED; SML0603

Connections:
3.3V: R10.1, R14.1, R22.1, R24.1, R71.2; also elsewhere on the board
5V: J1.1, J4.1, SJ26.1; also elsewhere on the board
AGND: C14.2, C15.2, C45.2, J12.1, J13.1, J14.1; also elsewhere on the board
AVCC: RN2.6 (2), RN2.7 (2), RN2.8 (2); also elsewhere on the board
GND: 3V3.C, C1.1, C19.1, C21.1, C22.1, J1.2, J2.2, J5.2, J6.2, J9.2, J11.2, L1.C, L2.C, L3.C, L4.C, LED10.C, VM.C; also elsewhere on the board
LED1: R12.2; also elsewhere on the board
LED2: R13.2; also elsewhere on the board
LED3: R49.2; also elsewhere on the board
LED4: R64.2; also elsewhere on the board
unnamed: R72.1, VM.A
unnamed: 3V3.A, R71.1
unnamed: LED10.A, R73.1
unnamed: L4.A, R64.1
unnamed: L3.A, R49.1
unnamed: L2.A, R13.1
unnamed: L1.A, R12.1
PLAY_LED: R73.2; also elsewhere on the board
TH1_HOTEND_1: C45.1, J12.2, RN2.2 (1); also elsewhere on the board
TH2_BED: C14.1, J13.2, RN2.1; also elsewhere on the board
TH3_HOTEND_2: C15.1, J14.2, RN2.3 (1); also elsewhere on the board
V-ENDSTOP: J5.1, J9.1, J11.1, SJ26.2
V-PROBE: J2.1, J4.2
VM: J4.3, J6.1, R72.2, SJ26.3; also elsewhere on the board
XMN: D7.C, J11.3
X_END_MIN: C1.2, D7.A, R24.2; also elsewhere on the board
YMN: D9.C, J9.3
Y_END_MIN: C19.2, D9.A, R22.2; also elsewhere on the board
ZMN: D11.C, J5.3
ZMX: D12.C, J2.3
Z_END_MAX: C22.2, D12.A, R10.2; also elsewhere on the board
Z_END_MIN: C21.2, D11.A, R14.2; also elsewhere on the board

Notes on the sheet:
Endstops
Thermistors
LED's
Spare HV

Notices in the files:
parts and their libraries:
SparkFun-PowerIC: Licensing: Creative Commons ShareAlike 4.0 International - https://creativecommons.org/licenses/by-sa/4.0
rc-master-smd: Copyright (C) 2007, Bob Starr
